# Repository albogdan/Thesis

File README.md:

## Thesis Repository 2021-2022
This is the repository for designing an end-to-end IoT system for large scale environmental monitoring. It integrates [CottonCandy](https://github.com/infernoDison/cottonCandy) on an Arduino with the ESP32 to create a Gateway. As well, it contains python scripts for sending data to Firebase Realtime Database, and reading it and adding it to Elasticsearch for display on

## File Hierarchy
### Arduino
Contains all the files for testing the Gateway and Nodes that run CottonCandy.

### ESP32
Contains various pieces and iterations of the ESP32 Gateway code. 
- `ESP32_MQTT` relates to integration of PubSubClient with the Mosquitto broker.
- `AdvancedWebServerESP32` deals with creating a web interface for management of various ESP32 Gateway parameters, such as WiFi and MQTT connections.
- `ESP32_Integrated_MQTT_WebServer` deals with integration of `AdvancedWebServerESP32` and `ESP32_MQTT`.

### Services
Contains services for data paths between `Mosquitto MQTT Broker`, `Firebase Realtime Database`, and `Elasticsearch`.
- `mqtt_firebase.py` deals with subscribing to topic from `Mosquitto` (the same one that the ESP32 Gateway publishes to) and uploading the received data to a `Firebase Realtime Database` document.
- `firebase_to_elasticsearch.py` deals with listening to events that a `Firebase Realtime Database` document publishes. It takes the event data and inserts it into an `Elasticsearch` instance, so Kibana can be used to visualize the data.

## ESP32/8266 Connect to UofT WiFi
* UofT WiFi is WPA2 Enterprise, so need a few extra commands. In the `setup()` method we replace  ```WiFi.begin(ssid, password);``` with

```C
// WPA2 enterprise magic starts here
WiFi.disconnect(true);
WiFi.mode(WIFI_STA);
esp_wifi_sta_wpa2_ent_set_identity((uint8_t *)EAP_ID, strlen(EAP_ID));
esp_wifi_sta_wpa2_ent_set_username((uint8_t *)EAP_USERNAME, strlen(EAP_USERNAME));
esp_wifi_sta_wpa2_ent_set_password((uint8_t *)EAP_PASSWORD, strlen(EAP_PASSWORD));
esp_wpa2_config_t config = WPA2_CONFIG_INIT_DEFAULT();
esp_wifi_sta_wpa2_ent_enable(&config);
// WPA2 enterprise magic ends here

WiFi.begin(ssid);
```
* As well, we add a couple of definitions and includes at the top of the file

```C
#include "esp_wpa2.h"
#define EAP_USERNAME "UTorID"
#define EAP_ID "UTorID"
#define EAP_PASSWORD "your_password"
```

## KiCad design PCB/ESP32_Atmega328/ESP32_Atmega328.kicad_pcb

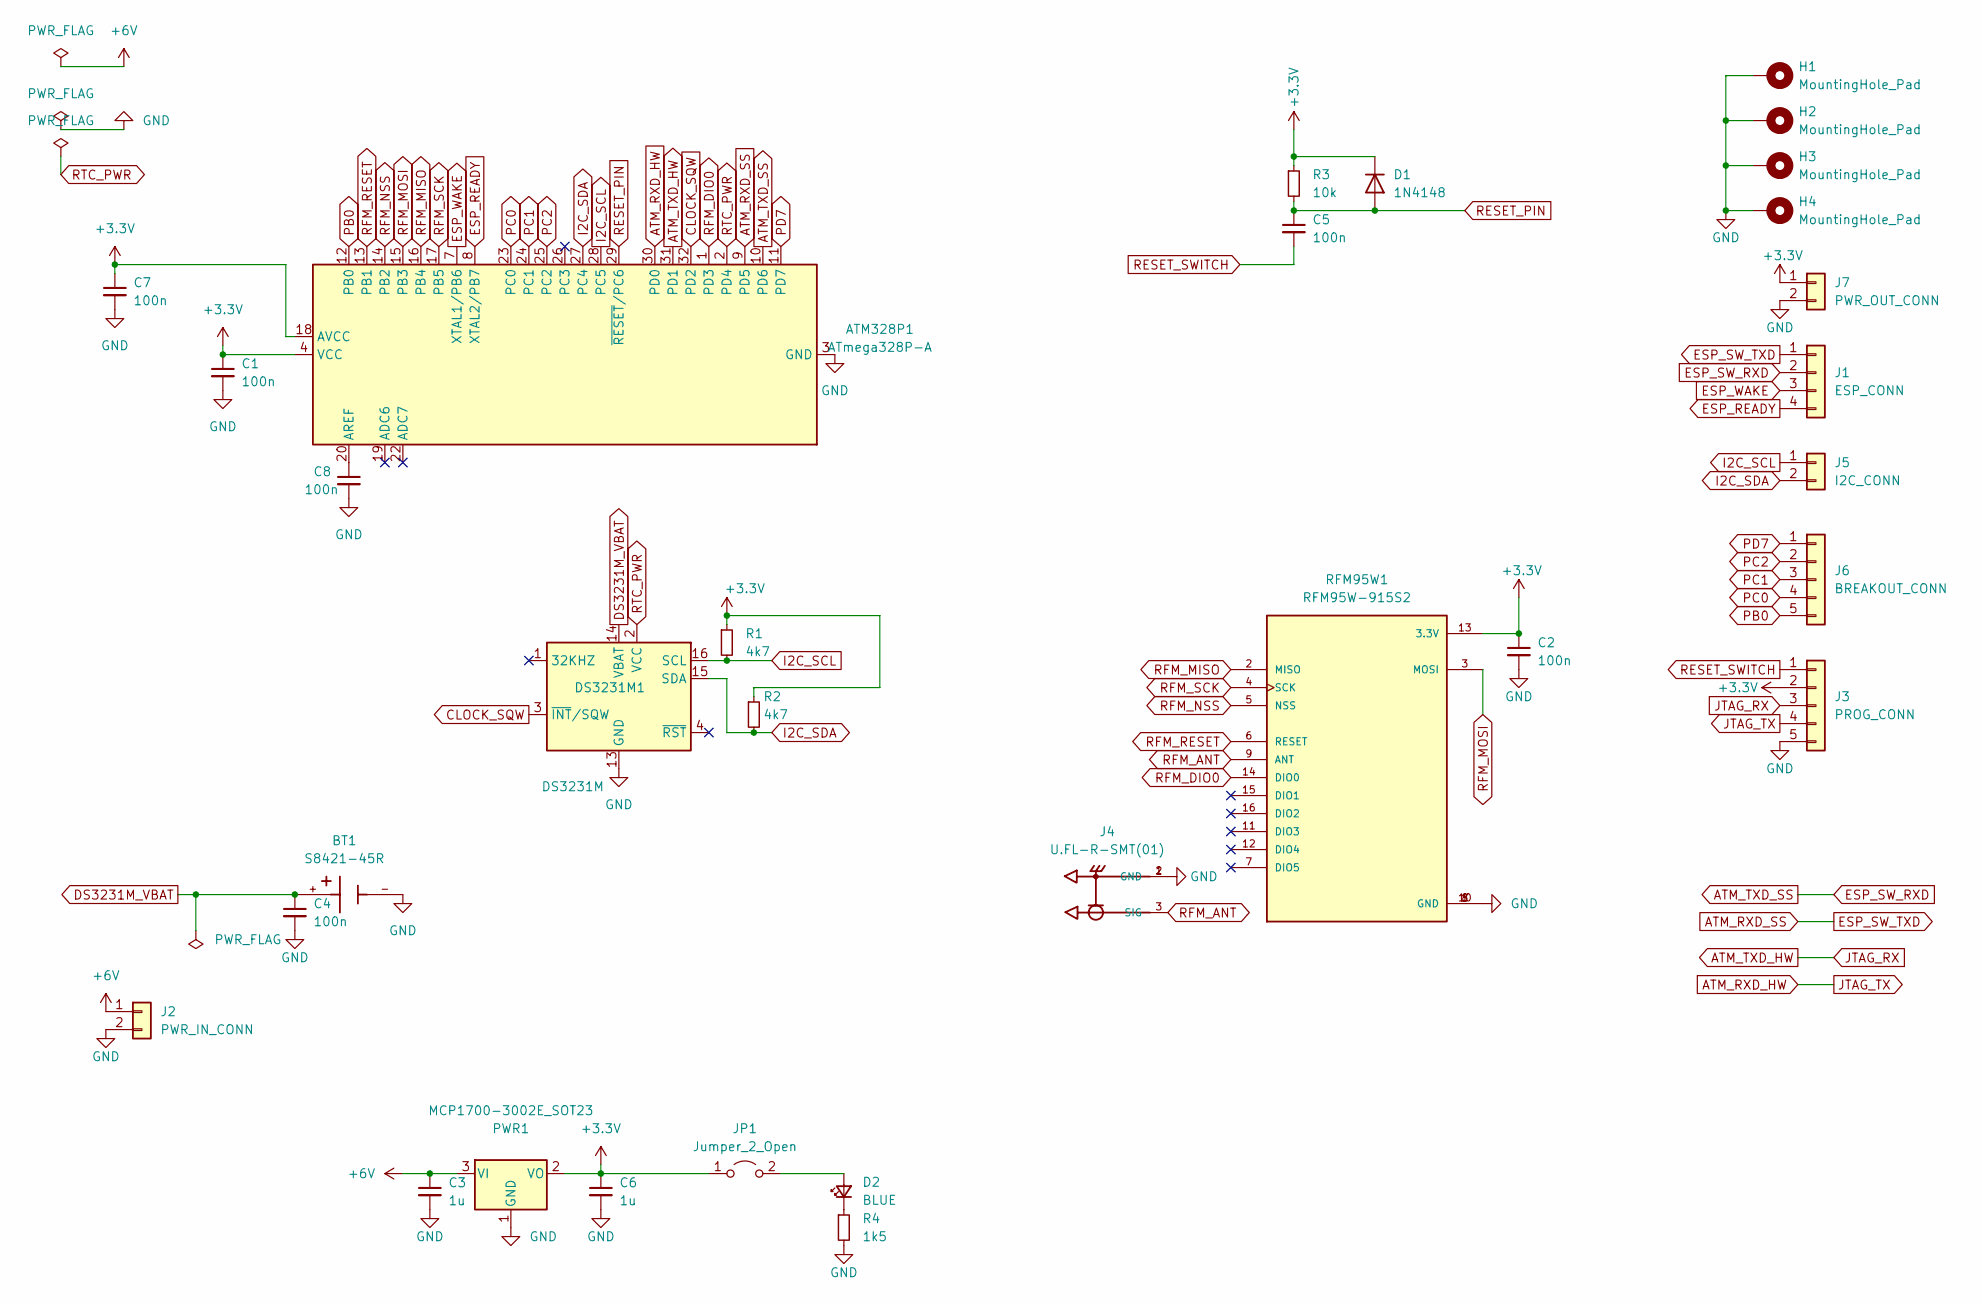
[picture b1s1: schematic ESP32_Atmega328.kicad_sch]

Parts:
ATM328P1: ATmega328P-A; TQFP-32_7x7mm_P0.8mm
BT1: S8421-45R; BAT_S8421-45R; PARTREV 5
C1, C2, C4, C5, C7, C8: 100n; C_0603_1608Metric
C3, C6: 1u; C_0603_1608Metric
D1: 1N4148; D_SOD-323
D2: BLUE; LED_0603_1608Metric
DS3231M1: DS3231M; SOIC-16W_7.5x10.3mm_P1.27mm
H1, H2, H3, H4: MountingHole_Pad
J1: ESP_CONN
J2: PWR_IN_CONN
J3: PROG_CONN; JST_XH_B5B-XH-A_1x05_P2.50mm_Vertical
J4: U.FL-R-SMT(01); HRS_U.FL-R-SMT(01)
J5: I2C_CONN; PinHeader_1x02_P2.54mm_Vertical
J6: BREAKOUT_CONN; PinHeader_1x05_P2.54mm_Vertical
J7: PWR_OUT_CONN; PinHeader_1x02_P2.54mm_Vertical
JP1: Jumper_2_Open; PinHeader_1x02_P2.54mm_Vertical
PWR1: MCP1700-3002E_SOT23; SOT-23
R1, R2: 4k7; R_0603_1608Metric
R3: 10k; R_0603_1608Metric
R4: 1k5; R_0603_1608Metric
RFM95W1: RFM95W-915S2; XCVR_RFM95W-915S2

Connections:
+3V3: ATM328P1.4 (VCC), ATM328P1.6 (VCC), ATM328P1.18 (AVCC), C1.1, C2.1, C6.1, C7.1, D1.1 (K), J3.2, J7.1, JP1.1 (A), PWR1.2 (VO), R1.1, R2.1, R3.1, RFM95W1.13 (3.3V)
+6V: C3.1, J2.1, PWR1.3 (VI)
ATM_RXD_HW: ATM328P1.30 (PD0), J3.4
ATM_RXD_SS: ATM328P1.9 (PD5), J1.1
ATM_TXD_HW: ATM328P1.31 (PD1), J3.3
ATM_TXD_SS: ATM328P1.10 (PD6), J1.2
CLOCK_SQW: ATM328P1.32 (PD2), DS3231M1.3 (~INT/SQW)
DS3231M_VBAT: BT1.+, C4.1, DS3231M1.14 (VBAT)
ESP_READY: ATM328P1.8 (XTAL2/PB7), J1.4
ESP_WAKE: ATM328P1.7 (XTAL1/PB6), J1.3
GND: ATM328P1.3 (GND), ATM328P1.5 (GND), ATM328P1.21 (GND), BT1.-, C1.2, C2.2, C3.2, C4.2, C6.2, C7.2, C8.2, DS3231M1.5 (GND), DS3231M1.6 (GND), DS3231M1.7 (GND), DS3231M1.8 (GND), DS3231M1.9 (GND), DS3231M1.10 (GND), DS3231M1.11 (GND), DS3231M1.12 (GND), DS3231M1.13 (GND), H1.1, H2.1, H3.1, H4.1, J2.2, J3.5, J4.1 (GND), J4.2 (GND), J7.2, PWR1.1 (GND), R4.2, RFM95W1.1 (GND), RFM95W1.8 (GND), RFM95W1.10 (GND)
I2C_SCL: ATM328P1.28 (PC5), DS3231M1.16 (SCL), J5.1, R1.2
I2C_SDA: ATM328P1.27 (PC4), DS3231M1.15 (SDA), J5.2, R2.2
unnamed: ATM328P1.20 (AREF), C8.1
unnamed: D2.1 (K), R4.1
unnamed: D2.2 (A), JP1.2 (B)
PB0: ATM328P1.12 (PB0), J6.5
PC0: ATM328P1.23 (PC0), J6.4
PC1: ATM328P1.24 (PC1), J6.3
PC2: ATM328P1.25 (PC2), J6.2
PD7: ATM328P1.11 (PD7), J6.1
RESET_PIN: ATM328P1.29 (~RESET/PC6), C5.1, D1.2 (A), R3.2
RESET_SWITCH: C5.2, J3.1
RFM_ANT: J4.3 (SIG), RFM95W1.9 (ANT)
RFM_DIO0: ATM328P1.1 (PD3), RFM95W1.14 (DIO0)
RFM_MISO: ATM328P1.16 (PB4), RFM95W1.2 (MISO)
RFM_MOSI: ATM328P1.15 (PB3), RFM95W1.3 (MOSI)
RFM_NSS: ATM328P1.14 (PB2), RFM95W1.5 (NSS)
RFM_RESET: ATM328P1.13 (PB1), RFM95W1.6 (RESET)
RFM_SCK: ATM328P1.17 (PB5), RFM95W1.4 (SCK)
RTC_PWR: ATM328P1.2 (PD4), DS3231M1.2 (VCC)

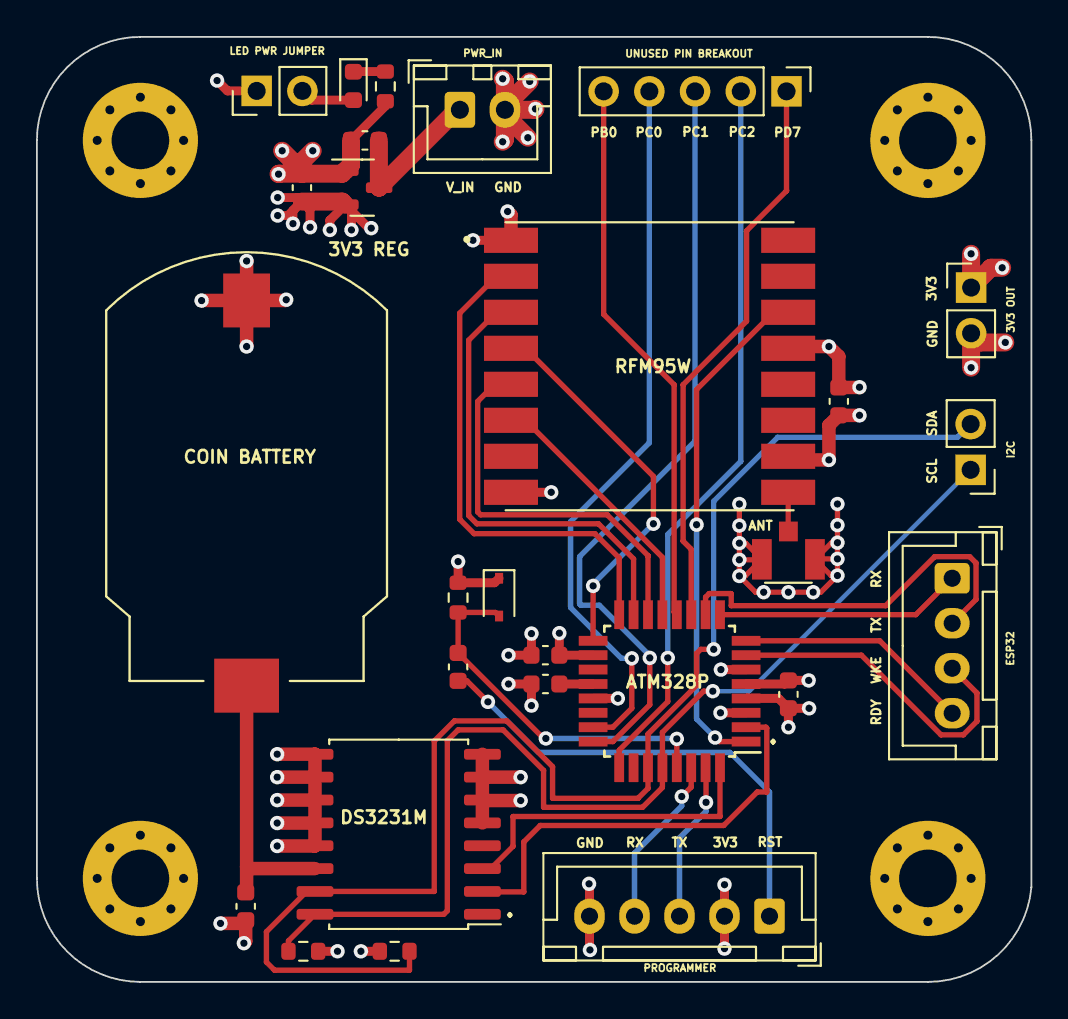
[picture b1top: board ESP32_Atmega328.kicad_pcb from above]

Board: 4 copper layers, 55.2 x 52.5 mm, 31 parts (0 on the bottom side), 31 nets.

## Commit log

2021-10-27 Initial commit with ESP32 working to connect to WiFi and MQTT server and send basic info to the mqtt server
2021-10-27 Functionality for reading from Serial2 on the ESP32 and publishing to the MQTT server
2021-10-28 Added information about WPA2 UofT Enterprise WiFi connection to ESP32
2021-10-28 Added hibernate functionality. Tested by setting system to sleep every 5000 loops for 10 seconds
2021-11-11 ESP32: Functionality for reading aggregated and non-aggregated packets from the Arduino Functionality for hibernating when a signal isn't heard from the Arduino for a period of time
    Arduino:
    Created random packets for aggregated and non-aggregated messages, sent randomly every number of seconds
    Added ability to flip a pin to high before sending messages, to tell the ESP32 to wake up from hibernation
2021-11-17 ESP32: - Added functionality to tell the Arduino when it has finished booting (i.e., its setup method). - Added free statements for mallocs that I forgot previously. Arduino: - Added functionality to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
2021-11-18 ESP32: - Implemented initial version of captive portal to set up WiFi information - Captive Portal also contains option to set up the server address and port for your MQTT broker - BUG: if the server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
2021-11-25 Seperated into multiple files
2021-11-25 Created AdvancedWebServer template, to use for the ESP32 WiFi/MQTT portal Created html/css/js pages to upload to the ESP32 to be served for the ESP32 WiFi/MQTT portal
2021-11-26 Added features to: Connect to WPA2 Personal or WPA2 Enterprise, depending on a dropdown Choose a custom AP SSID and password Modified MQTT.ino to connect to a password-protected MQTT Broker
    Modified the HTML files:
    "Clear all credentials" -> "Reset all configurations"
    Added a dropdown for WPA2 Personal and WPA2 Enterprise, in WiFi STA Config
    Added a username and password field for the MQTT Config
    Added a page to change AP SSID and Password
    Added jQuery for using the dropdown to show and hide the WPA2 Personal and Enterprise forms
2022-01-02 Seperated Server and WiFi functionality Renamed some files
2022-01-02 Added functionality for default username and password mqtt server Added functionality for default integration with CottonCandy
2022-01-02 Gateway and Node .ino files for the Arduino
2022-01-02 Integrated the AdvancedWebServer and the ESP_MQTT for packet parsing, together into a complete minimum viable product
2022-01-02 mqtt_firebase: Subscribes to a topic (that the ESP32 publishes data to) and writes that data to the Firebase Realtime Database insert_from_json_into_realtime_database: test script for inserting data 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
2022-01-02 Custom Portal (#1)
    * Seperated into multiple files
    * Created AdvancedWebServer template, to use for the ESP32 WiFi/MQTT portal
    Created html/css/js pages to upload to the ESP32 to be served for the ESP32 WiFi/MQTT portal
    * Added features to:
    Connect to WPA2 Personal or WPA2 Enterprise, depending on a dropdown
    Choose a custom AP SSID and password
2022-01-02 Custom portal (#2)
    * Seperated into multiple files
    * Created AdvancedWebServer template, to use for the ESP32 WiFi/MQTT portal
    Created html/css/js pages to upload to the ESP32 to be served for the ESP32 WiFi/MQTT portal
    * Added features to:
    Connect to WPA2 Personal or WPA2 Enterprise, depending on a dropdown
    Choose a custom AP SSID and password
2022-02-10 Updated file hierarchy
2022-02-10 Added support for temperature data as a float
2022-02-10 Moved AdvancedWebServerESP32 to be within the ESP32 folder
2022-02-10 Removed test script for inserting into realtime database
2022-02-16 Standalone test case for Cellular MQTT integration using TinyGSM library
2022-02-23 Added comments for specifying various 802.11 modes
2022-02-23 Added src files for webpage, and gateway_mode file on top
2022-02-28 Integrated web page commands for cellular and wifi interchange
2022-02-28 Tested TinyGSM with SoftwareSerial
2022-02-28 Removed extra import and updated name of overloaded now variable
2022-02-28 Added backend code for setting Gateway Mode Removed old piece of unused code
2022-02-28 Added return info on the connectToWiFi function for whether the connection is APSTA or just AP (i.e., if STA connection fails or not)
2022-02-28 Update the now variable through update_current_local_time() function, each time an MQTT message is sent
2022-02-28 Added support for SIM7600X Cellular module, using TinyGSM library
2022-03-02 Updated Serial Baud Rate to 57600 from 115200, since SoftwareSerial library for the ESP32 does not work with 115200 for some reason
2022-03-02 Black formatting
2022-03-02 Data and graphs for ESP32 Profiling
2022-03-02 Data and graphs for ESP32 802.11BGN tests
2022-03-03 Added data for ESP32 Cellular Profiling with the Cellular block always on
2022-03-10 Updated graphs
2022-03-10 Changed gateway_mode to uplink_mode
2022-03-10 Added FSM diagrams
2022-03-10 Fixed gateway to uplink text
2022-03-17 Updated FSM to remove background
2022-03-17 Added Circuit Diagram and Timeline for interactions between the uplink and downlink
2022-03-24 Updated Diagrams for Circuit and Timeline, added Website Diagrams
2022-03-24 Added graphs for message counts
2022-03-24 Added cellular profiling measurements
2022-03-29 Cellular mqtt client
2022-03-31 Updated FSM diagrams
2022-03-31 Updated ArduinoGateway with new pre- and post- callbacks
2022-03-31 Updated cellular connection
2022-03-31 Added ability to publish a test message to MQTT
2022-03-31 Fixed packet parsing decimal places
2022-03-31 Sleep settings updated
2022-03-31 Added CottonCandy, with pre and post callbacks
2022-04-11 Updated serial interface speed
2022-04-11 Diagrams
2022-04-11 Graphs
2022-05-12 Version 1 PCB design for CottonCandy Nodes
2022-05-16 Added parts, rerouted some, added component zips
2022-05-18 Antenna impedance matching to 50ohms, and added more ground vias around the antenna connector
2022-05-18 Reduced power consumption for ESP32 HUZZAH board to 65uA in deep sleep mode, while maintaining ability to wake from a pin. Added profiling data for the lower sleep current as well. Note that base wak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
2022-06-21 Added dual core version of the software
2022-06-22 First Integration with google-arduino-iot code
2022-06-28 Fixed MQTT.ino to compile properly
2022-06-28 save
2022-06-29 Weird issue
2022-06-29 Integrated SDCard writing into the code
2022-06-29 Added TODOs to remap pins due to SD Card module having to use pins 5,18,19 (VSPI) since HSPI does not work (send the ESP32 into an infinite boot loop)
2022-07-04 Receiving config and publishhing message
2022-07-11 Integrated SD CARD
2022-07-12 Small update
2022-07-29 Hand off

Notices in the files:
PCB/ESP32_Atmega328/ESP32_Atmega328.kicad_pcb:
Copyright © 2022
